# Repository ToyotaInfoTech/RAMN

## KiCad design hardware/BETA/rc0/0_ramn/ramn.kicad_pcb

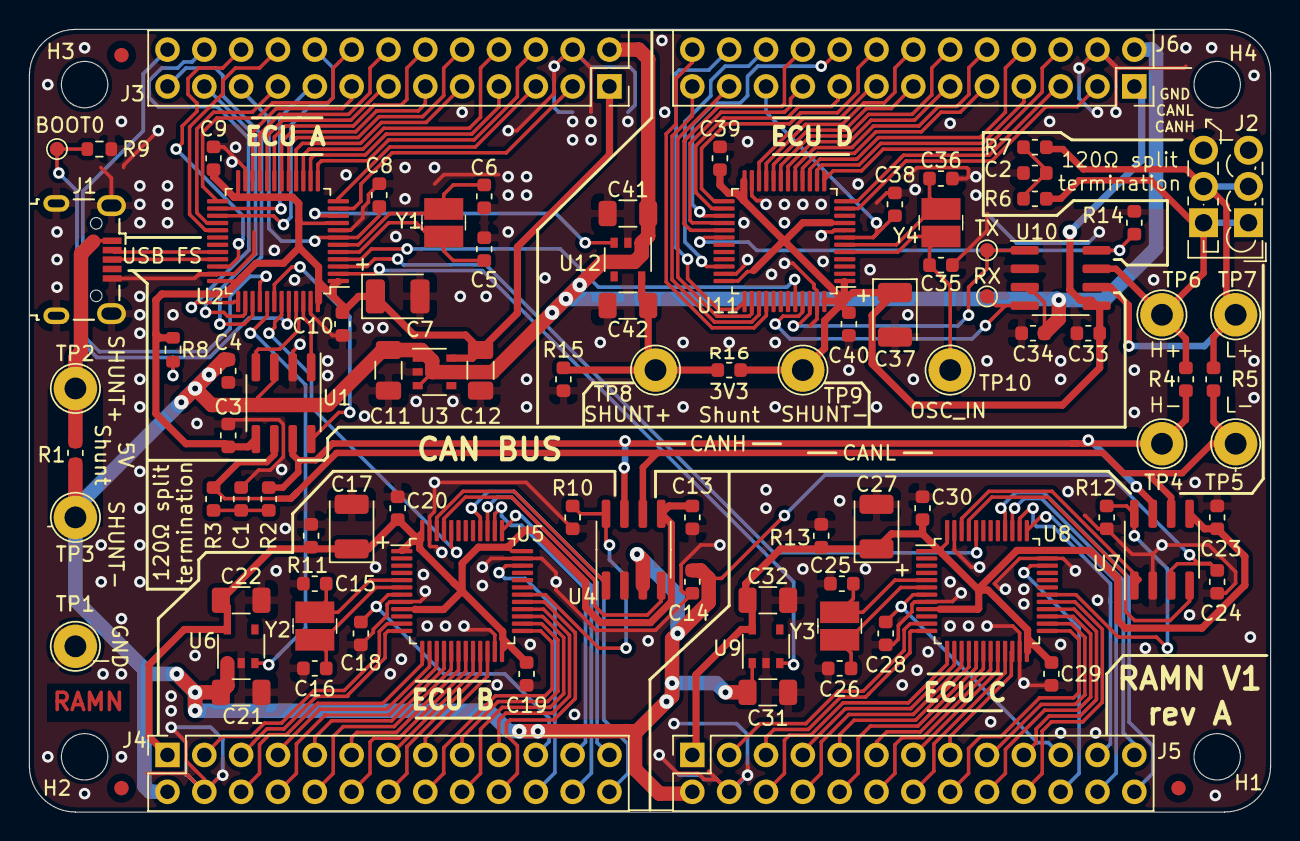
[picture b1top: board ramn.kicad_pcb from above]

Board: 2 copper layers, 85.6 x 54.0 mm, 100 parts (0 on the bottom side), 135 nets.

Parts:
 : Fiducial; Fiducial_1mm_Mask2mm
 #2,  #3: Fiducial; Fiducial_1mm_Mask2mm
BOOT0: TestPoint_Pad_D1.0mm
C1, C2: 1nF; C_0603_1608Metric
C3, C4, C8, C9, C10, C13, C14, C18, C19, C20, C23, C24, C28, C29, C30, C33, C34, C38, C39, C40: 100nF; C_0603_1608Metric
C5, C6, C15, C16, C25, C26, C35, C36: 10pF; C_0603_1608Metric
C7, C17, C27, C37: 10uF; CP_EIA-3528-15_AVX-H
C11, C12, C21, C22, C31, C32, C41, C42: 1uF; C_1206_3216Metric
H1, H2, H3, H4: MountingHole; MountingHole_3.2mm_M3_ISO7380
J1: USB_C_Micro; USB_Micro-B_Wuerth_629105150521
J2: Screw_Terminal_01x03; TerminalBlock_Phoenix_PTSM-0,5-3-2.5-V-THR_1x03_P2.50mm_Ver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
J3, J4, J5, J6: PinSocket_2x13_P2.54mm_Vertical
R1, R4, R5, R16: 0R; R_0603_1608Metric
R2, R3, R6, R7: 60R; R_0603_1608Metric
R8: DNM; R_0603_1608Metric
R9, R10, R11, R12, R13, R14, R15: 10k; R_0603_1608Metric
RX: TestPoint_Pad_D1.0mm
TP1, TP2, TP3, TP4, TP5, TP6, TP7, TP8, TP9, TP10: TestPoint_Loop_D2.54mm_Drill1.5mm_Beaded
TX: TestPoint_Pad_D1.0mm
U1, U4, U7, U10: ATA6561-GAQW-N; SOIC-8_3.9x4.9mm_P1.27mm
U2, U5, U8, U11: STM32L443CCTx; LQFP-48_7x7mm_P0.5mm
U3, U6, U9, U12: NCV8163; TSOP-5_1.65x3.05mm_P0.95mm
Y1, Y2, Y3, Y4: NX3225GD-8MHZ-STD-CRA-3; SMD-2_3.2x2.5mm

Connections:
+5V: C4.1, C11.1, C14.1, C21.1, C24.1, C31.1, C34.1, C41.1, J3.2, J4.2, J5.2, J6.2, R1.1, TP3.1, U1.3, U3.1, U3.3, U4.3, U6.1, U7.3, U9.1, U10.3, U12.1
/ECUB/3V3_ECU: C13.1, C17.1, C19.1, C20.1, C22.1, J4.1, R11.1, U4.5, U5.1, U5.9, U5.24, U5.36, U5.48, U6.5
/ECUB/BOOT0: U2.43, U5.44
/ECUB/CAN1_RX: U4.4, U5.45
/ECUB/CAN1_TX: U4.1, U5.46
/ECUB/CANH_IN: R2.1, R4.2, TP4.1, U1.7, U4.7, U7.7
/ECUB/CANL_IN: R3.2, R5.2, TP5.1, U1.6, U4.6, U7.6
/ECUB/CAN_STB: R10.1, U4.8, U5.30
/ECUB/PA1: J4.3, U5.11
/ECUB/PA2: J4.5, U5.12
/ECUB/PA3: J4.6, U5.13
/ECUB/PA4: J4.7, U5.14
/ECUB/PA5: J4.8, U5.15
/ECUB/PA6: J4.9, U5.16
/ECUB/PA7: J4.10, U5.17
/ECUB/PA8: J4.20, U5.29
/ECUB/PB0: J4.11, U5.18
/ECUB/PB1: J4.12, U5.19
/ECUB/PB2: J4.13, U5.20
/ECUB/PB10: J4.14, U5.21
/ECUB/PB11: J4.15, U5.22
/ECUB/PB12: J4.16, U5.25
/ECUB/PB13: J4.17, U5.26
/ECUB/PB14: J4.18, U5.27
/ECUB/PB15: J4.19, U5.28
/ECUB/SYS_JTCK-SWCLK: J4.24, U5.37
/ECUB/SYS_JTDI: J4.23, U5.38
/ECUB/SYS_JTDO-SWO: J4.25, U5.39
/ECUB/SYS_JTMS-SWDIO: J4.22, U5.34
/ECUB/SYS_JTRST: J4.26, U5.40
/ECUB/nRST: C18.1, J4.21, U5.7
/ECUC/3V3_ECU: C23.1, C27.1, C29.1, C30.1, C32.1, J5.1, R13.1, U7.5, U8.1, U8.9, U8.24, U8.36, U8.48, U9.5
/ECUC/BOOT0: U2.3, U8.44
/ECUC/CAN1_RX: U7.4, U8.45
/ECUC/CAN1_TX: U7.1, U8.46
/ECUC/CAN_STB: R12.1, U7.8, U8.30
/ECUC/PA1: J5.3, U8.11
/ECUC/PA2: J5.5, U8.12
/ECUC/PA3: J5.6, U8.13
/ECUC/PA4: J5.7, U8.14
/ECUC/PA5: J5.8, U8.15
/ECUC/PA6: J5.9, U8.16
/ECUC/PA7: J5.10, U8.17
/ECUC/PA8: J5.20, U8.29
/ECUC/PB0: J5.11, U8.18
/ECUC/PB1: J5.12, U8.19
/ECUC/PB2: J5.13, U8.20
/ECUC/PB10: J5.14, U8.21
/ECUC/PB11: J5.15, U8.22
/ECUC/PB12: J5.16, U8.25
/ECUC/PB13: J5.17, U8.26
/ECUC/PB14: J5.18, U8.27
/ECUC/PB15: J5.19, U8.28
/ECUC/SYS_JTCK-SWCLK: J5.24, U8.37
/ECUC/SYS_JTDI: J5.23, U8.38
/ECUC/SYS_JTDO-SWO: J5.25, U8.39
/ECUC/SYS_JTMS-SWDIO: J5.22, U8.34
/ECUC/SYS_JTRST: J5.26, U8.40
/ECUC/nRST: C28.1, J5.21, U8.7
/ECUD/3V3_ECU: C33.1, C37.1, C39.1, C40.1, J6.1, R16.1, TP9.1, U10.5, U11.1, U11.9, U11.24, U11.36, U11.48
/ECUD/BOOT0: U2.4, U11.44
/ECUD/CAN1_RX: RX.1, U10.4, U11.45
/ECUD/CAN1_TX: TX.1, U10.1, U11.46
/ECUD/CANH_IN: J2.1, R4.1, R6.1, TP6.1, U10.7
/ECUD/CANL_IN: J2.2, R5.1, R7.2, TP7.1, U10.6
/ECUD/CAN_STB: R14.1, U10.8, U11.30
/ECUD/PA1: J6.3, U11.11
/ECUD/PA2: J6.5, U11.12
/ECUD/PA3: J6.6, U11.13
/ECUD/PA4: J6.7, U11.14
/ECUD/PA5: J6.8, U11.15
/ECUD/PA6: J6.9, U11.16
/ECUD/PA7: J6.10, U11.17
/ECUD/PA8: J6.20, U11.29
/ECUD/PB0: J6.11, U11.18
/ECUD/PB1: J6.12, U11.19
/ECUD/PB2: J6.13, U11.20
/ECUD/PB10: J6.14, U11.21
/ECUD/PB11: J6.15, U11.22
/ECUD/PB12: J6.16, U11.25
/ECUD/PB13: J6.17, U11.26
/ECUD/PB14: J6.18, U11.27
/ECUD/PB15: J6.19, U11.28
/ECUD/SYS_JTCK-SWCLK: J6.24, U11.37
/ECUD/SYS_JTDI: J6.23, U11.38
/ECUD/SYS_JTDO-SWO: J6.25, U11.39
/ECUD/SYS_JTMS-SWDIO: J6.22, U11.34
/ECUD/SYS_JTRST: J6.26, U11.40
/ECUD/nRST: C38.1, J6.21, U11.7
/ECUD/sheet5D7F273B/3.3V: C42.1, R15.1, R16.2, TP8.1, U12.5
/usb_uc/3V3_ECU: C3.1, C7.1, C9.1, C10.1, C12.1, J3.1, R8.1, U1.5, U2.1, U2.9, U2.24, U2.36, U2.48, U3.5
/usb_uc/BOOT0: BOOT0.1, R8.2, R9.1, U2.44
/usb_uc/CAN1_RX: U1.4, U2.45
/usb_uc/CAN1_TX: U1.1, U2.46
/usb_uc/CAN_STB: U1.8, U2.42
/usb_uc/ECU_1_EN: U2.41, U6.3
/usb_uc/ECU_2_EN: U2.2, U9.3
/usb_uc/ECU_3_EN: U2.10, U12.3
/usb_uc/PA1: J3.3, U2.11
/usb_uc/PA2: J3.5, U2.12
/usb_uc/PA3: J3.6, U2.13
/usb_uc/PA4: J3.7, U2.14
/usb_uc/PA5: J3.8, U2.15
/usb_uc/PA6: J3.9, U2.16
/usb_uc/PA7: J3.10, U2.17
/usb_uc/PA8: J3.20, U2.29
/usb_uc/PB0: J3.11, U2.18
/usb_uc/PB1: J3.12, U2.19
/usb_uc/PB2: J3.13, U2.20
/usb_uc/PB10: J3.14, U2.21
/usb_uc/PB11: J3.15, U2.22
/usb_uc/PB12: J3.16, U2.25
/usb_uc/PB13: J3.17, U2.26
/usb_uc/PB14: J3.18, U2.27
/usb_uc/PB15: J3.19, U2.28
/usb_uc/SYS_JTCK-SWCLK: J3.24, U2.37
/usb_uc/SYS_JTDI: J3.23, U2.38
/usb_uc/SYS_JTDO-SWO: J3.25, U2.39
/usb_uc/SYS_JTMS-SWDIO: J3.22, U2.34
/usb_uc/SYS_JTRST: J3.26, U2.40
/usb_uc/USB_D+: J1.3, U2.33
/usb_uc/USB_D-: J1.2, U2.32
/usb_uc/nRST: C8.1, J3.21, U2.7
GND: C1.2, C2.2, C3.2, C4.2, C5.2, C6.2, C7.2, C8.2, C9.2, C10.2, C11.2, C12.2, C13.2, C14.2, C15.2, C16.2, C17.2, C18.2, C19.2, C20.2, C21.2, C22.2, C23.2, C24.2, C25.2, C26.2, C27.2, C28.2, C29.2, C30.2, C31.2, C32.2, C33.2, C34.2, C35.2, C36.2, C37.2, C38.2, C39.2, C40.2, C41.2, C42.2, J1.5, J1.6, J2.3, J3.4, J4.4, J5.4, J6.4, R9.2, R10.2, R11.2, R12.2, R13.2, R14.2, R15.2, TP1.1, U1.2, U2.8, U2.23, U2.35, U2.47, U3.2, U4.2, U5.8, U5.23, U5.35, U5.47, U6.2, U7.2, U8.8, U8.23, U8.35, U8.47, U9.2, U10.2, U11.8, U11.23, U11.35, U11.47, U12.2
unnamed: C1.1, R2.2, R3.1
unnamed: C2.1, R6.2, R7.1
unnamed: C5.1, U2.5, Y1.1
unnamed: C6.1, U2.6, Y1.2
unnamed: C15.1, U5.5, Y2.1
unnamed: C16.1, U5.6, Y2.2
unnamed: C25.1, U8.5, Y3.1
unnamed: C26.1, U8.6, Y3.2
unnamed: C35.1, TP10.1, U11.5, Y4.1
unnamed: C36.1, U11.6, Y4.2
unnamed: J1.1, R1.2, TP2.1

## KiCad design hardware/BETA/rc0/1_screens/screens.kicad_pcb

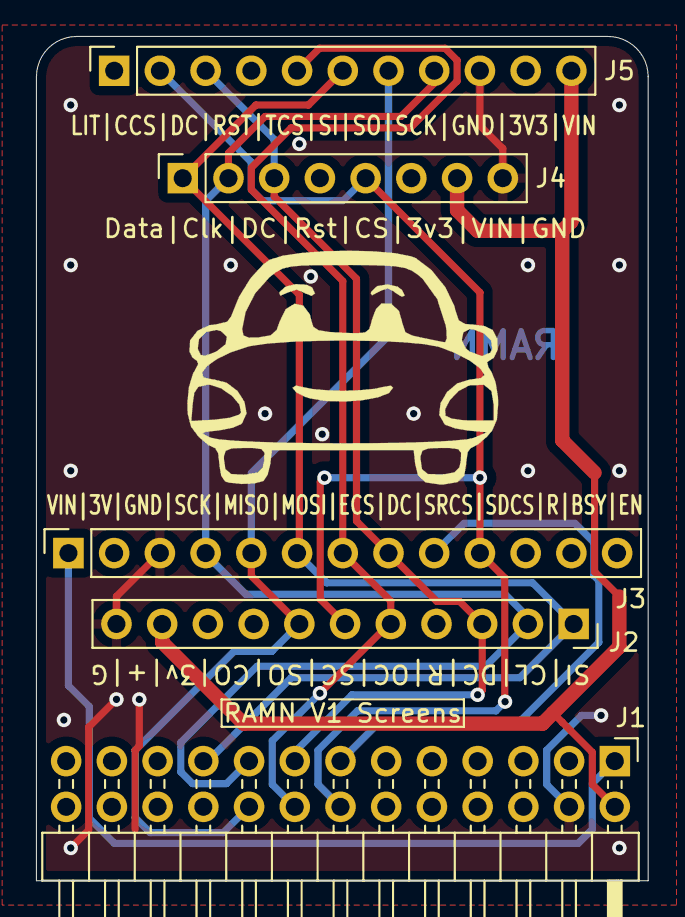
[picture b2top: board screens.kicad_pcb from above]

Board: 2 copper layers, 34.0 x 46.9 mm, 5 parts (0 on the bottom side), 10 nets.

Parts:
J1: PinHeader_2x13_P2.54mm_Horizontal
J2: 1431; PinSocket_1x11_P2.54mm_Vertical
J3: 4086; PinSocket_1x13_P2.54mm_Vertical
J4: 326; PinSocket_1x08_P2.54mm_Vertical
J5: 4383; PinSocket_1x11_P2.54mm_Vertical

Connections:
+5V: J1.2, J2.10, J4.7, J5.11
/3V3_ECU: J1.1, J3.1
DC: J1.15, J2.3, J3.8, J4.3, J5.3
GND: J1.4, J2.11, J3.3, J4.8, J5.9
LCD_CS: J1.16, J2.5, J3.7, J5.5
MISO: J1.18, J2.7, J3.5, J5.7
MOSI: J1.19, J2.1, J3.6, J4.1, J5.6
SCK: J1.17, J2.2, J3.4, J4.2, J5.8
SD_CS: J1.14, J2.6, J3.10, J4.5, J5.2
SRAM_CS: J1.13, J3.9

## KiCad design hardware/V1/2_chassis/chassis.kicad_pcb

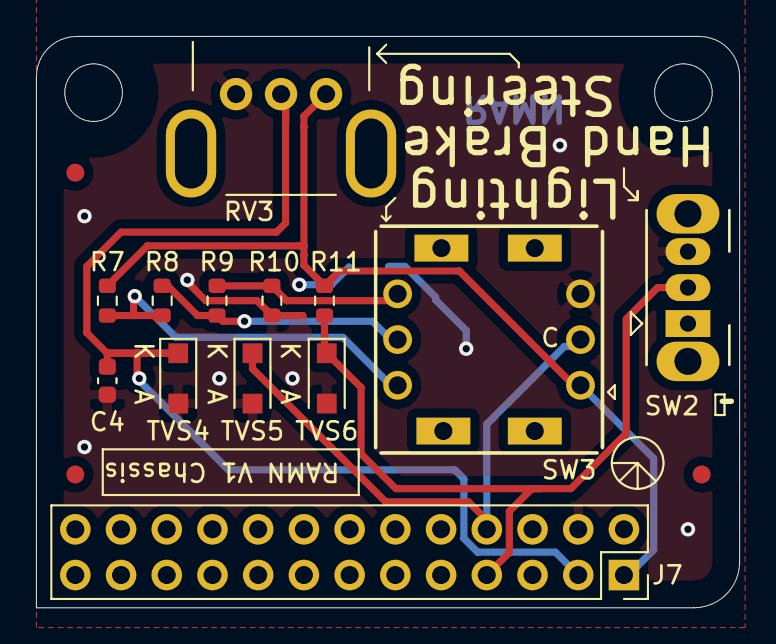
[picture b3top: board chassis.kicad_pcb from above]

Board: 2 copper layers, 39.1 x 31.7 mm, 18 parts (0 on the bottom side), 8 nets.

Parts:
C4: 100nF; C_0603_1608Metric
FID1, FID2, FID3: Fiducial; Fiducial_1mm_Mask2mm
H3, H4: MountingHole; MountingHole_3.2mm_M3_ISO7380
J7: PinSocket_2x13_P2.54mm_Vertical
R7, R8, R9, R10, R11: 10k; R_0603_1608Metric
RV3: R_POT_TRIM_US; RK09K1110A2S
SW2: SW_CuK_OS102011MA1QN1_SPDT_Angled
SW3: NKK_NR01; NR01
TVS4, TVS5, TVS6: D_TVS; D_SOD-123F

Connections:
/3V3_ECU: J7.1, R7.1, R11.2, RV3.1, SW3.1
GND: C4.2, J7.4, R10.2, RV3.3, SW2.3, SW3.5, TVS4.2, TVS5.2, TVS6.2
Lamp: J7.8, SW3.3, TVS5.1
unnamed: R7.2, R8.1, SW3.2
unnamed: R8.2, R9.1, SW3.4
unnamed: R9.2, R10.1, SW3.6
SW1: J7.7, R11.1, SW2.2, TVS6.1
Wheel: C4.1, J7.3, RV3.2, TVS4.1

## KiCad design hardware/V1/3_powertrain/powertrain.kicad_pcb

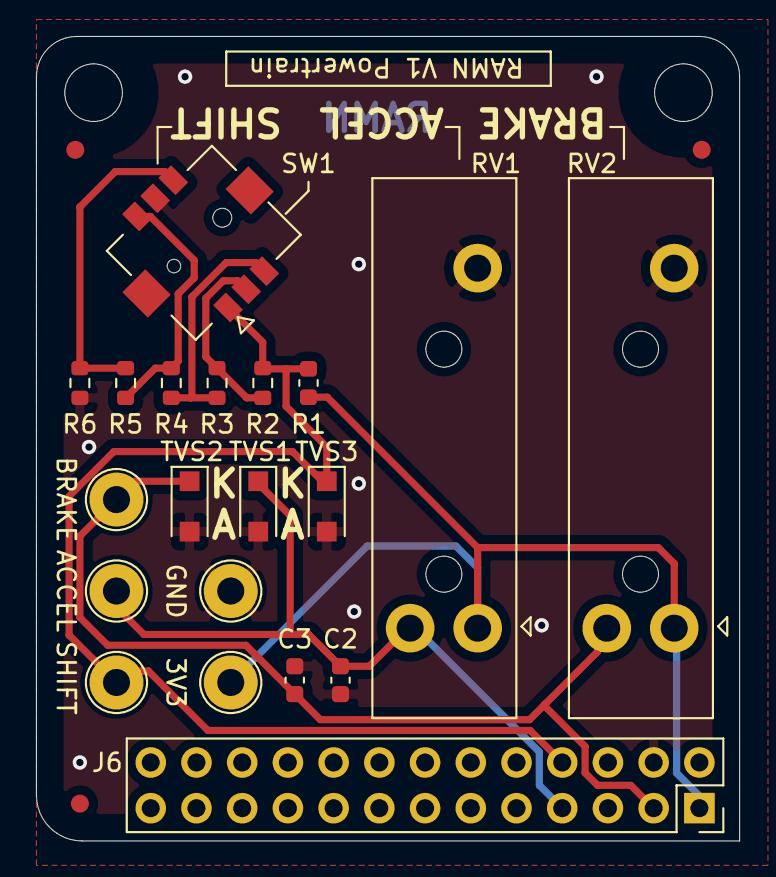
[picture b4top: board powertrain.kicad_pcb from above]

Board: 2 copper layers, 39.1 x 44.7 mm, 25 parts (0 on the bottom side), 9 nets.

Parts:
3V3: TestPoint; TestPoint_Loop_D2.54mm_Drill1.5mm_Beaded
ACCEL: TestPoint; TestPoint_Loop_D2.54mm_Drill1.5mm_Beaded
BRAKE: TestPoint; TestPoint_Loop_D2.54mm_Drill1.5mm_Beaded
C2, C3: 100nF; C_0603_1608Metric
FID1, FID2, FID3: Fiducial; Fiducial_1mm_Mask2mm
GND: TestPoint; TestPoint_Loop_D2.54mm_Drill1.5mm_Beaded
H1, H2: MountingHole; MountingHole_3.2mm_M3_ISO7380
J6: PinSocket_2x13_P2.54mm_Vertical
R1, R2, R3, R4, R5, R6: 10k; R_0603_1608Metric
RV1, RV2: R_POT_TRIM_US; RS15111A900B
SHIFT: TestPoint; TestPoint_Loop_D2.54mm_Drill1.5mm_Beaded
SW1: SKRHADE010
TVS1, TVS2, TVS3: D_TVS; D_SOD-123F

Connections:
/3V3_ECU: 3V3.1, J6.1, R1.1, RV1.1, RV2.1
Accel: ACCEL.1, C2.1, J6.7, RV1.2, TVS1.1
Brake: BRAKE.1, C3.1, J6.3, RV2.2, TVS2.1
GND: C2.2, C3.2, GND.1, J6.4, R6.2, RV1.3, RV2.3, SW1.5, TVS1.2, TVS2.2, TVS3.2
JOYSTICK: J6.8, R1.2, R2.1, SHIFT.1, SW1.1, TVS3.1
unnamed: R2.2, R3.1, SW1.2
unnamed: R3.2, R4.1, SW1.3
unnamed: R4.2, R5.1, SW1.4
unnamed: R5.2, R6.1, SW1.6

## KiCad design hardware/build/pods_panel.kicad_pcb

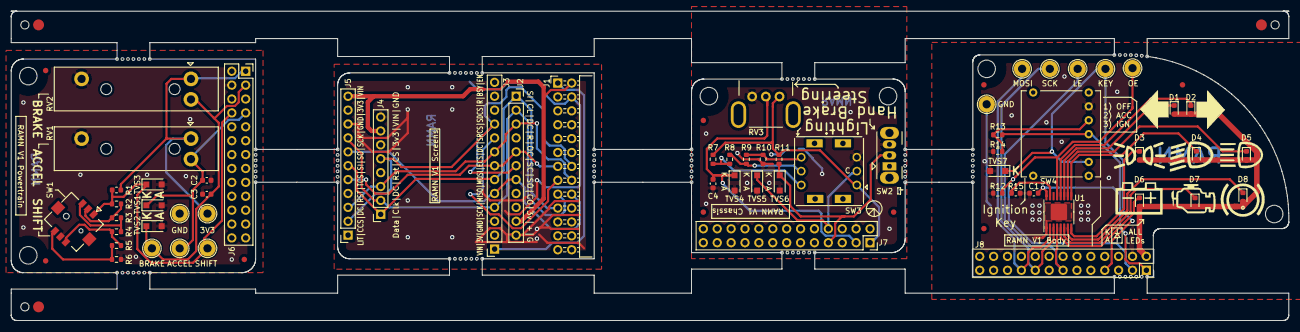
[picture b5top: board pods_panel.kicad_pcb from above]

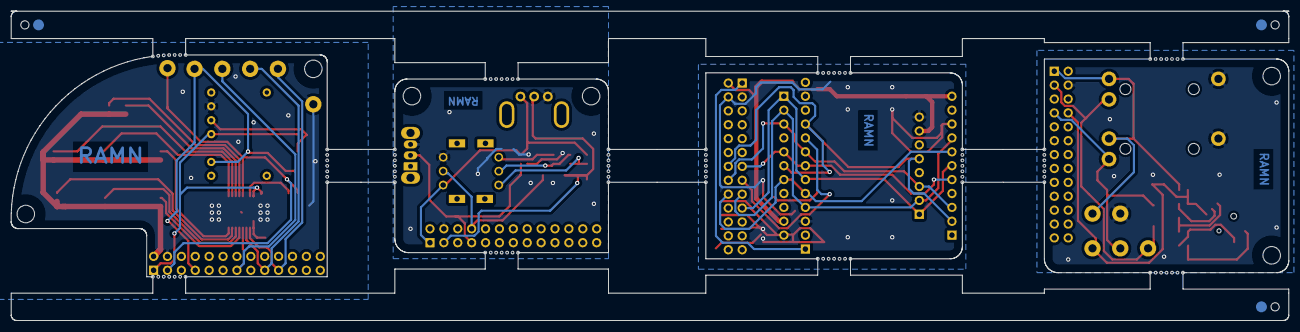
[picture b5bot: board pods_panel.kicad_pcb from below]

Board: 2 copper layers, 233.6 x 56.6 mm, 183 parts (3 on the bottom side), 45 nets.

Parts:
3V3: TestPoint; TestPoint_Loop_D2.54mm_Drill1.5mm_Beaded
ACCEL: TestPoint; TestPoint_Loop_D2.54mm_Drill1.5mm_Beaded
BRAKE: TestPoint; TestPoint_Loop_D2.54mm_Drill1.5mm_Beaded
C1, C2, C3, C4: 100nF; C_0603_1608Metric
D1, D2, D3, D4, D5, D6, D7, D8: LED; LED_0603_1608Metric
FID1, FID1#2, FID1#3, FID2, FID2#2, FID2#3, FID3, FID3#2, FID3#3: Fiducial; Fiducial_1mm_Mask2mm
GND: TestPoint; TestPoint_Loop_D2.54mm_Drill1.5mm_Beaded
GND#2: TestPoint; TestPoint_Loop_D2.54mm_Drill1.5mm_Beaded
H1, H2, H3, H4, H5, H6: MountingHole; MountingHole_3.2mm_M3_ISO7380
J1: PinHeader_2x13_P2.54mm_Horizontal
J2: 1431; PinSocket_1x11_P2.54mm_Vertical
J3: 4086; PinSocket_1x13_P2.54mm_Vertical
J4: 326; PinSocket_1x08_P2.54mm_Vertical
J5: 4383; PinSocket_1x11_P2.54mm_Vertical
J6, J7, J8: PinSocket_2x13_P2.54mm_Vertical
KEY: TestPoint; TestPoint_Loop_D2.54mm_Drill1.5mm_Beaded
KiKit_FID_B_1, KiKit_FID_B_2, KiKit_FID_B_3: Fiducial
KiKit_FID_T_1, KiKit_FID_T_2, KiKit_FID_T_3: Fiducial
KiKit_MB_1_1, KiKit_MB_1_2, KiKit_MB_1_3, KiKit_MB_1_4, KiKit_MB_1_5, KiKit_MB_1_6, KiKit_MB_1_7, KiKit_MB_2_1, KiKit_MB_2_2, KiKit_MB_2_3, KiKit_MB_2_4, KiKit_MB_2_5, KiKit_MB_2_6, KiKit_MB_2_7, KiKit_MB_3_1, KiKit_MB_3_2, KiKit_MB_3_3, KiKit_MB_3_4, KiKit_MB_3_5, KiKit_MB_3_6, KiKit_MB_3_7, KiKit_MB_4_1, KiKit_MB_4_2, KiKit_MB_4_3, KiKit_MB_4_4, KiKit_MB_4_5, KiKit_MB_4_6, KiKit_MB_4_7, KiKit_MB_5_1, KiKit_MB_5_2, KiKit_MB_5_3, KiKit_MB_5_4, KiKit_MB_5_5, KiKit_MB_5_6, KiKit_MB_5_7, KiKit_MB_6_1, KiKit_MB_6_2, KiKit_MB_6_3, KiKit_MB_6_4, KiKit_MB_6_5, KiKit_MB_6_6, KiKit_MB_6_7, KiKit_MB_7_1, KiKit_MB_7_2, KiKit_MB_7_3, KiKit_MB_7_4, KiKit_MB_7_5, KiKit_MB_7_6, KiKit_MB_7_7, KiKit_MB_8_1, KiKit_MB_8_2, KiKit_MB_8_3, KiKit_MB_8_4, KiKit_MB_8_5, KiKit_MB_8_6, KiKit_MB_8_7, KiKit_MB_9_1, KiKit_MB_9_2, KiKit_MB_9_3, KiKit_MB_9_4, KiKit_MB_9_5, KiKit_MB_9_6, KiKit_MB_9_7, KiKit_MB_10_1, KiKit_MB_10_2, KiKit_MB_10_3, KiKit_MB_10_4, KiKit_MB_10_5, KiKit_MB_10_6, KiKit_MB_10_7, KiKit_MB_11_1, KiKit_MB_11_2, KiKit_MB_11_3, KiKit_MB_11_4, KiKit_MB_11_5, KiKit_MB_11_6, KiKit_MB_11_7, KiKit_MB_12_1, KiKit_MB_12_2, KiKit_MB_12_3, KiKit_MB_12_4, KiKit_MB_12_5, KiKit_MB_12_6, KiKit_MB_12_7, KiKit_MB_13_1, KiKit_MB_13_2, KiKit_MB_13_3, KiKit_MB_13_4, KiKit_MB_13_5, KiKit_MB_13_6, KiKit_MB_13_7, KiKit_MB_14_1, KiKit_MB_14_2, KiKit_MB_14_3, KiKit_MB_14_4, KiKit_MB_14_5, KiKit_MB_14_6, KiKit_MB_14_7: NPTH
KiKit_TO_1, KiKit_TO_2, KiKit_TO_3: NPTH
LE: TestPoint; TestPoint_Loop_D2.54mm_Drill1.5mm_Beaded
MOSI: TestPoint; TestPoint_Loop_D2.54mm_Drill1.5mm_Beaded
OE: TestPoint; TestPoint_Loop_D2.54mm_Drill1.5mm_Beaded
R1, R2, R3, R4, R5, R6, R7, R8, R9, R10, R11, R12, R13, R14: 10k; R_0603_1608Metric
R15: 1.8k; R_0603_1608Metric
RV1, RV2: R_POT_TRIM_US; RS15111A900B
RV3: R_POT_TRIM_US; RK09K1110A2S
SCK: TestPoint; TestPoint_Loop_D2.54mm_Drill1.5mm_Beaded
SHIFT: TestPoint; TestPoint_Loop_D2.54mm_Drill1.5mm_Beaded
SW1: SKRHADE010
SW2: SW_CuK_OS102011MA1QN1_SPDT_Angled
SW3: NKK_NR01; NR01
SW4: SK14EG13
TVS1, TVS2, TVS3, TVS4, TVS5, TVS6, TVS7: D_TVS; D_SOD-123F
U1: STP08CP05XT; HTSSOP-16-1EP_4.4x5mm_P0.65mm_EP3x3mm

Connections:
Board_0-+5V: D1.2, D2.2, D3.2, D4.2, D5.2, D6.2, D7.2, D8.2, J8.2
Board_0-/3V3_ECU: C1.1, J8.1, R13.2, SW4.3, U1.16
Board_0-GND: C1.2, GND.1, J8.4, R12.1, R14.1, R15.1, SW4.1, TVS7.2, U1.1, U1.17
Board_0-Key: J8.7, KEY.1, SW4.C1, TVS7.1
Board_0-LE: J8.13, LE.1, U1.4
Board_0-MOSI: J8.19, MOSI.1, U1.2
Board_0-Net-(D1-Pad1): D1.1, U1.11
Board_0-Net-(D2-Pad1): D2.1, U1.12
Board_0-Net-(D3-Pad1): D3.1, U1.8
Board_0-Net-(D4-Pad1): D4.1, U1.9
Board_0-Net-(D5-Pad1): D5.1, U1.10
Board_0-Net-(D6-Pad1): D6.1, U1.5
Board_0-Net-(D7-Pad1): D7.1, U1.6
Board_0-Net-(D8-Pad1): D8.1, U1.7
Board_0-Net-(R13-Pad1): R13.1, R14.2, SW4.2
Board_0-Net-(R15-Pad2): R15.2, U1.15
Board_0-OE: J8.3, OE.1, R12.2, U1.13
Board_0-SCK: J8.17, SCK.1, U1.3
Board_1-+5V: J1.2, J2.10, J4.7, J5.11
Board_1-/3V3_ECU: J1.1, J3.1
Board_1-DC: J1.16, J2.3, J3.8, J4.3, J5.3
Board_1-GND: J1.4, J2.11, J3.3, J4.8, J5.9
Board_1-LCD_CS: J1.13, J2.5, J3.7, J5.5
Board_1-MISO: J1.18, J2.7, J3.5, J5.7
Board_1-MOSI: J1.19, J2.1, J3.6, J4.1, J5.6
Board_1-SCK: J1.17, J2.2, J3.4, J4.2, J5.8
Board_1-SD_CS: J1.14, J2.6, J3.10, J4.5, J5.2
Board_1-SRAM_CS: J1.15, J3.9
Board_2-/3V3_ECU: 3V3.1, J6.1, R1.1, RV1.1, RV2.1
Board_2-Accel: ACCEL.1, C2.1, J6.7, RV1.2, TVS1.1
Board_2-Brake: BRAKE.1, C3.1, J6.3, RV2.2, TVS2.1
Board_2-GND: C2.2, C3.2, GND#2.1, J6.4, R6.2, RV1.3, RV2.3, SW1.5, TVS1.2, TVS2.2, TVS3.2
Board_2-JOYSTICK: J6.8, R1.2, R2.1, SHIFT.1, SW1.1, TVS3.1
Board_2-Net-(R2-Pad2): R2.2, R3.1, SW1.2
Board_2-Net-(R3-Pad2): R3.2, R4.1, SW1.3
Board_2-Net-(R4-Pad2): R4.2, R5.1, SW1.4
Board_2-Net-(R5-Pad2): R5.2, R6.1, SW1.6
Board_3-/3V3_ECU: J7.1, R7.1, R11.2, RV3.1, SW3.1
Board_3-GND: C4.2, J7.4, R10.2, RV3.3, SW2.3, SW3.5, TVS4.2, TVS5.2, TVS6.2
Board_3-Lamp: J7.8, SW3.3, TVS5.1
Board_3-Net-(R7-Pad2): R7.2, R8.1, SW3.2
Board_3-Net-(R8-Pad2): R8.2, R9.1, SW3.4
Board_3-Net-(R10-Pad1): R9.2, R10.1, SW3.6
Board_3-SW1: J7.7, R11.1, SW2.2, TVS6.1
Board_3-Wheel: C4.1, J7.3, RV3.2, TVS4.1
